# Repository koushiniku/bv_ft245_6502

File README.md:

# replACIA USB to W65xx Bus Adapter

*This board is still in development.*

This is a replacement for a number of "serial port" solutions for
W65Cxx-based breadboard computers requiring either the W65C51N ACIA or
custom logic and either a MAX232 and DB9 connector or breakout board with
a serial-to-USB or parallel-to-USB chip.

This solution replaces all that on a single board with a FTDI FT245R (aka.
USB Blaster) chip and some logic ICs, all on a 8x5 DIP16 board, which is
smaller than the 14x6 DIP28 ACIA. The board supports USB2.0 with vertical
USB.C connector.

## Pin List

Pin | Name | Type | Description
--- | ---- | ---- | -----------
1 | &phiv;2 | Input | PHI2: The system clock.
2 | CS# | Input | Chip Select from the address decode logic.
3 | R/W# | Input | RWB signal from the CPU.
4 | GND | Power Input | Ground.
5 | V<sub>CC</sub> | Power Input | +5V DC. (+3.3V is unsupported without adding a 12 MHz crystal or upgrading to FT245RN.)
6 | A0 | Input | Address bit 0 from the CPU.
7 | IRQ# | Open Drain Output | Interrupt to the CPU indicating received data is ready to be read. (If you prefer a push-pull interrupt output, replace the 74LVC1G38 with a 74LVC1G00.)
8 | RES# | Input | RESB reset signal from the CPU. This clears the interrupt enable register.
9&ndash;16 | D0&ndash;D7 | Input/Output | The CPU data bus.

## Register 0 &mdash; CSR

Bit | Name | Type | Description
--- | ---- | ---- | -----------
7 | TXE# | Read-Only | If cleared to 0, the transmit buffer is empty and ready to be written to. (Yes, it actually works!)
6 | RXF# | Read-Only | If cleared to 0, the receive buffer is full and has data ready to be read from.
5 | PWREN# | Read-Only | This is the status of the PWREN# signal from the FT245R. If cleared to 0, the device has been configured by USB. If set to 1, the device is in USB suspend mode. This can be used by software as indicating something similar to DSR#.
4 | VBUS | Read-Only | This is the status of USB power. If set to 1, USB is powered, indicating the remote host should be resent. If cleared to 0, the FT245RN device is in reset. This can be used by software as something similar to DCD#.
3:1 | Reserved | Unused |
0 | IRQ_EN | Read/Write | Set to 1 to enable the receive interrupt. The default reset value is 0 (disabled). There is no transmit interrupt; I assumed USB is fast enough that polling TXE# is sufficient. (The ACIA oddly enables the receive interrupt by default.)

## Register 1 &mdash; DATA

When receive data is present, reading from this register returns a byte of
data received from the remote host. This also clears the IRQ (if it was
enabled). When the transmit buffer is empty, writing to this register
transmits a byte of data to the remote host.

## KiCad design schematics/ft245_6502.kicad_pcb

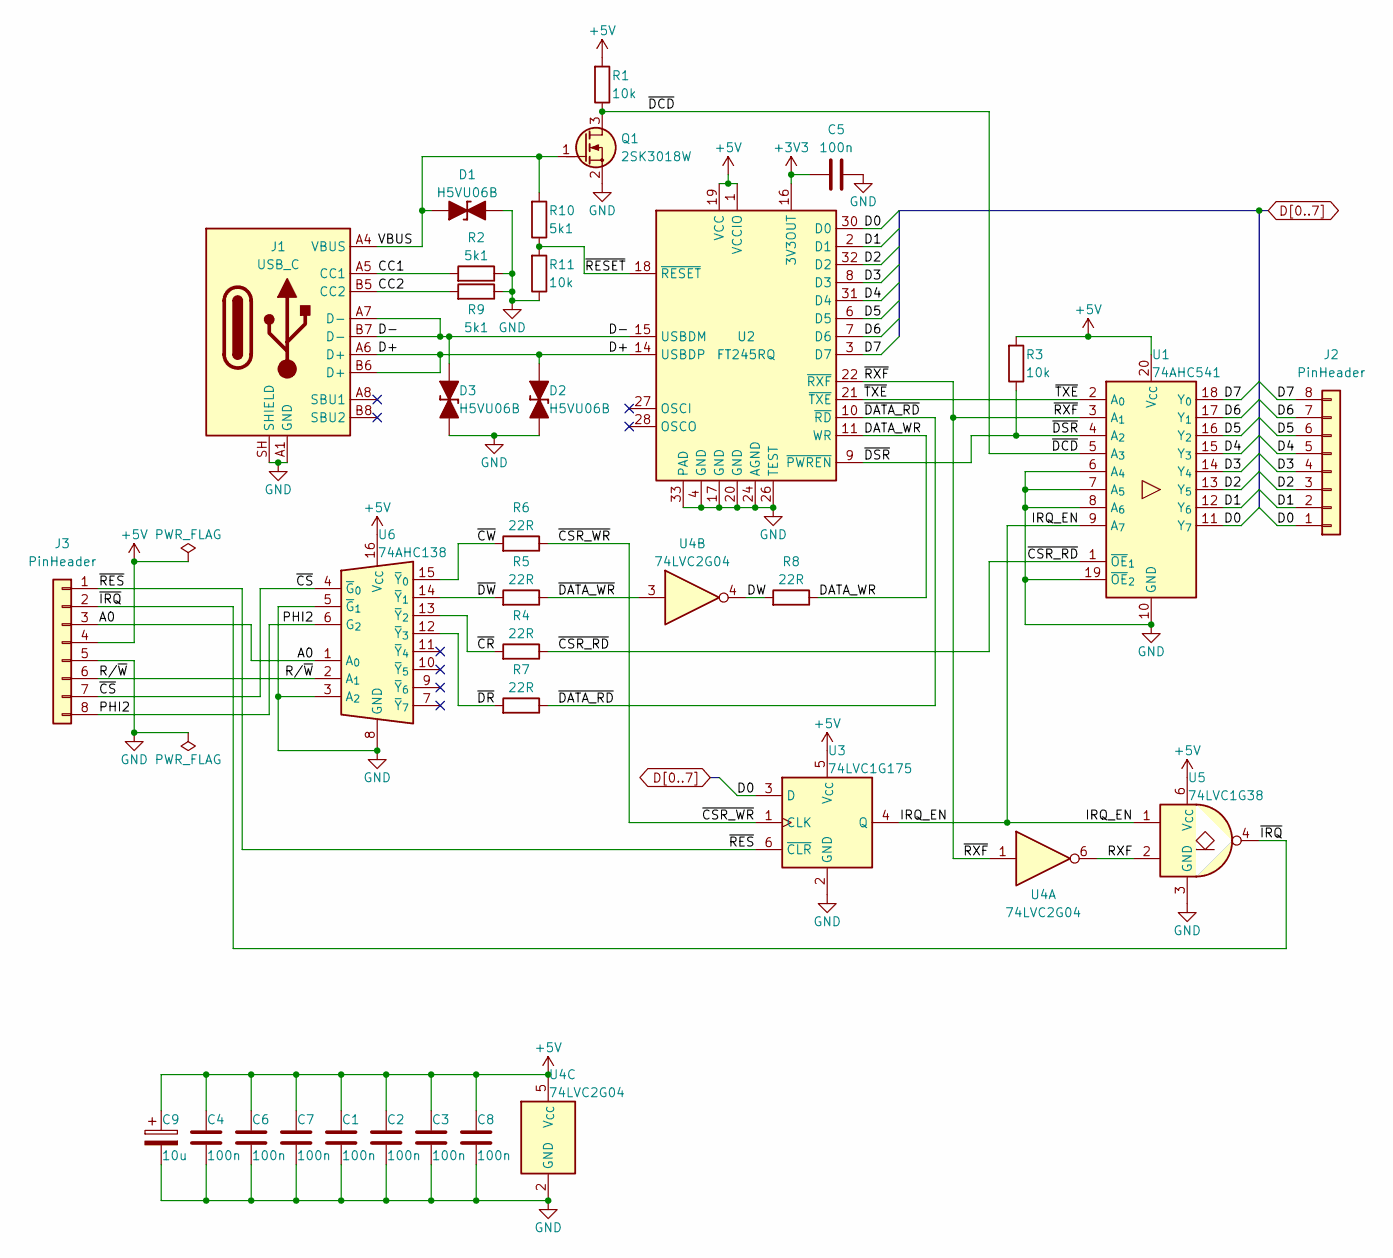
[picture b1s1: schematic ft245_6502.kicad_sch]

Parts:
C1, C2, C3, C4, C5, C6, C7, C8: 100n; C_0402; LCSC C1525
C9: 10u; TAJA106K016RNJ; LCSC C7171
D1, D2, D3: H5VU06B; LCSC C20615780
J1: USB_C; USB_C_Vertical_16P; LCSC C49118464
J2, J3: PinHeader; PinHeader_1x08_P2.54mm_Vertical
Q1: 2SK3018W; SOT-323_SC-70; LCSC C20069149
R1, R3, R11: 10k; R_0402; LCSC C25744
R2, R9, R10: 5k1; R_0402; LCSC C25905
R4, R5, R6, R7, R8: 22R; R_0402; LCSC C25092
U1: 74AHC541; NXP_SOT764-1_DHVQFN20_MO-241_4.5x2.5mm; LCSC C554414
U2: FT245RQ; FTDI_QFN-32_5x5mm; LCSC C1550574
U3: 74LVC1G175; NXP_SOT886_XSON6_MO-252_1x1.45mm; LCSC C548286
U4: 74LVC2G04; NXP_SOT886_XSON6_MO-252_1x1.45mm; LCSC C426707
U5: 74LVC1G38; NXP_SOT886_XSON6_MO-252_1x1.45mm; LCSC C54929569
U6: 74AHC138; NXP_SOT763-1_DHVQFN16_MO-241_3.5x2.4mm; LCSC C554237

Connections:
+3V3: C5.1, U2.16 (3V3OUT)
+5V: C1.1, C2.1, C3.1, C4.1, C6.1, C7.1, C8.1, C9.1, J3.4, R1.1, R3.1, U1.20 (V_{CC}), U2.1 (VCCIO), U2.19 (VCC), U3.5 (V_{CC}), U4.5 (V_{CC}), U5.6 (V_{CC}), U6.16 (V_{CC})
/A0: J3.3, U6.1 (A_{0})
/CC1: J1.A5 (CC1), R2.1
/CC2: J1.B5 (CC2), R9.1
/D+: D2.2 (A), J1.A6 (D+), J1.B6 (D+), U2.14 (USBDP)
/D-: D3.2 (A), J1.A7 (D-), J1.B7 (D-), U2.15 (USBDM)
/DATA_WR: R8.2, U2.11 (WR)
/DW: R8.1, U4.4
/IRQ_EN: U1.9 (A_{7}), U3.4 (Q), U5.1
/PHI2: J3.8, U6.6 (G_{2})
/RXF: U4.6, U5.2
/R/~W: J3.6, U6.2 (A_{1})
/VBUS: D1.2 (A), J1.A4 (VBUS), J1.A9 (VBUS), J1.B4 (VBUS), J1.B9 (VBUS), Q1.1 (G), R10.1
/~CR: R4.1, U6.13 (~Y_{2})
/~CSR_RD: R4.2, U1.1 (~OE_{1})
/~CSR_WR: R6.2, U3.1 (CLK)
/~CS: J3.7, U6.4 (~G_{0})
/~CW: R6.1, U6.15 (~Y_{0})
/~DATA_RD: R7.2, U2.10 (~RD)
/~DATA_WR: R5.2, U4.3
/~DCD: Q1.3 (D), R1.2, U1.5 (A_{3})
/~DR: R7.1, U6.12 (~Y_{3})
/~DSR: R3.2, U1.4 (A_{2}), U2.9 (~PWREN)
/~DW: R5.1, U6.14 (~Y_{1})
/~IRQ: J3.2, U5.4
/~RESET: R10.2, R11.1, U2.18 (~RESET)
/~RES: J3.1, U3.6 (~CLR)
/~RXF: U1.3 (A_{1}), U2.22 (~RXF), U4.1
/~TXE: U1.2 (A_{0}), U2.21 (~TXE)
D0: J2.1, U1.11 (Y_{7}), U2.30 (D0), U3.3 (D)
D1: J2.2, U1.12 (Y_{6}), U2.2 (D1)
D2: J2.3, U1.13 (Y_{5}), U2.32 (D2)
D3: J2.4, U1.14 (Y_{4}), U2.8 (D3)
D4: J2.5, U1.15 (Y_{3}), U2.31 (D4)
D5: J2.6, U1.16 (Y_{2}), U2.6 (D5)
D6: J2.7, U1.17 (Y_{1}), U2.7 (D6)
D7: J2.8, U1.18 (Y_{0}), U2.3 (D7)
GND: C1.2, C2.2, C3.2, C4.2, C5.2, C6.2, C7.2, C8.2, C9.2, D1.1 (K), D2.1 (K), D3.1 (K), J1.A1 (GND), J1.A12 (GND), J1.B1 (GND), J1.B12 (GND), J1.SH (SHIELD), J3.5, Q1.2 (S), R2.2, R9.2, R11.2, U1.6 (A_{4}), U1.7 (A_{5}), U1.8 (A_{6}), U1.10 (GND), U1.19 (~OE_{2}), U1.21 (PAD), U2.4 (GND), U2.17 (GND), U2.20 (GND), U2.24 (AGND), U2.26 (TEST), U2.33 (PAD), U3.2 (GND), U4.2 (GND), U5.3 (GND), U6.3 (A_{2}), U6.5 (~G_{1}), U6.8 (GND), U6.17 (PAD)

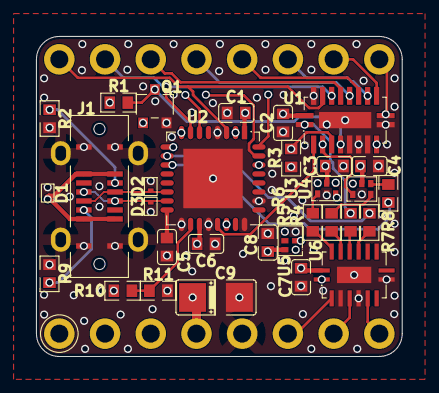
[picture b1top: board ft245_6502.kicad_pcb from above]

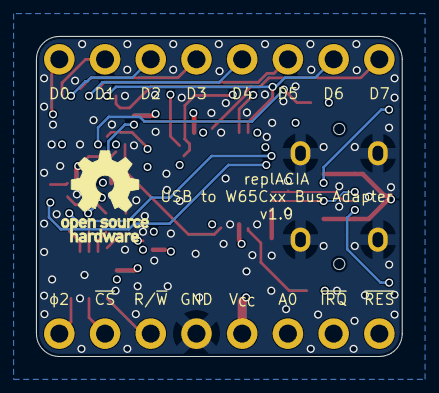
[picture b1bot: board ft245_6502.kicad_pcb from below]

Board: 6 copper layers, 20.3 x 17.8 mm, 33 parts (2 on the bottom side), 39 nets.
